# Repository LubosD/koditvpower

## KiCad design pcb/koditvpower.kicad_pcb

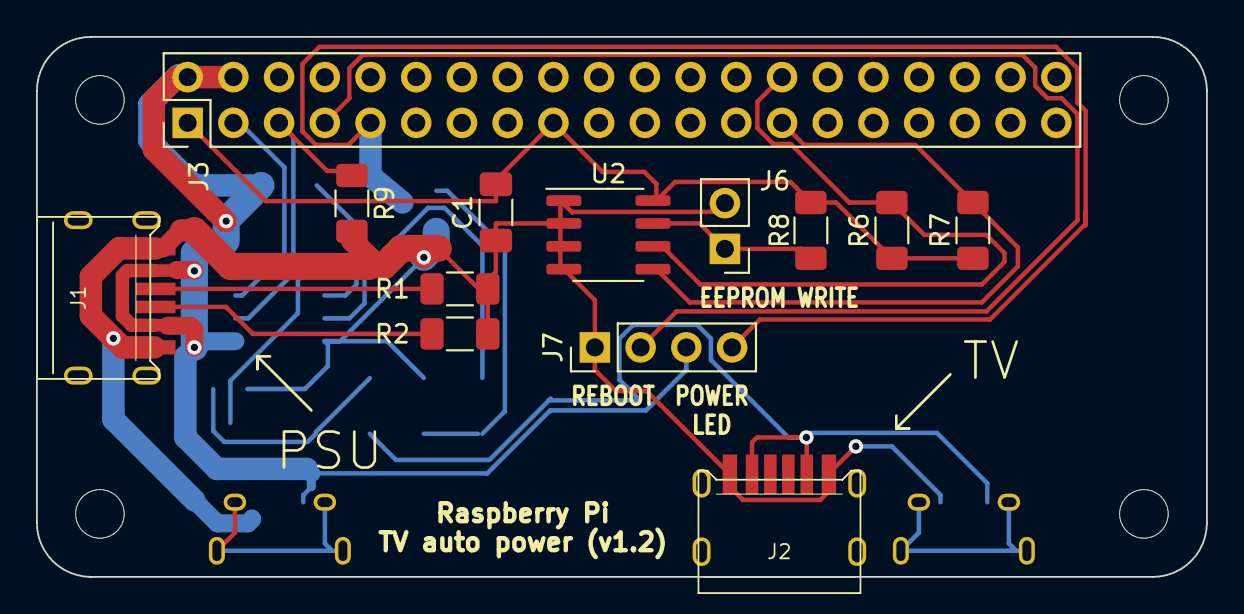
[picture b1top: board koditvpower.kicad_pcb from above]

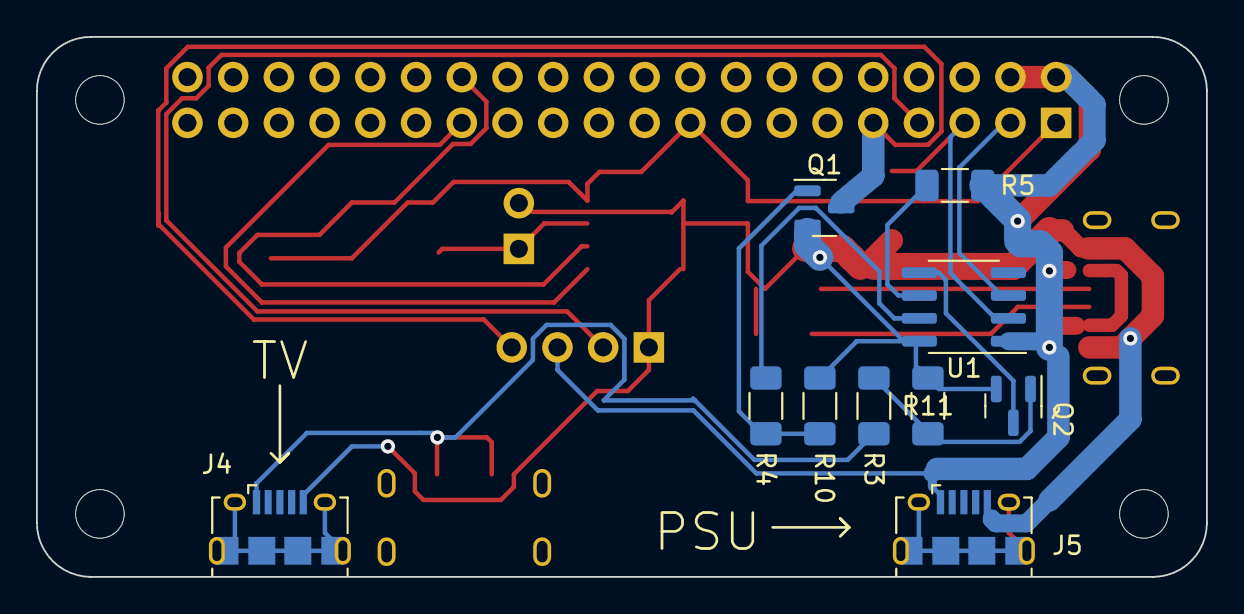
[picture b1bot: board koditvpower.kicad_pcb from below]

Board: 2 copper layers, 65.0 x 30.0 mm, 27 parts (10 on the bottom side), 18 nets.

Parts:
C1: C 100n; C_1206_3216Metric_Pad1.33x1.80mm_HandSolder
H1, H2, H3, H4: MountingHole_2.7mm_M2.5
J1: USB_C_MAIN; TYPE-C-31-M-17_handsolder
J2: USB_C_TV; TYPE-C-31-M-17_handsolder
J3: Raspberry_Pi_2_3; PinHeader_2x20_P2.54mm_Vertical
J4: USB_B_Micro_TV; USB_Micro-B_Amphenol_10118194_Horizontal
J5: USB_B_Micro_MAIN; USB_Micro-B_Amphenol_10118194_Horizontal
J6: EEPROM WRITE; PinHeader_1x02_P2.54mm_Vertical
J7: POWER LED / REBOOT KEY; PinHeader_1x04_P2.54mm_Vertical
Q1: AO3400; SOT-23
Q2: BSS138; SOT-23
R1, R2: R 5k1; R_1206_3216Metric_Pad1.30x1.75mm_HandSolder
R3: R1k; R_1206_3216Metric_Pad1.30x1.75mm_HandSolder
R4: R 1k; R_1206_3216Metric_Pad1.30x1.75mm_HandSolder
R5, R9, R10, R11: R10k; R_1206_3216Metric_Pad1.30x1.75mm_HandSolder
R6, R7: R 3.9K; R_1206_3216Metric_Pad1.30x1.75mm_HandSolder
R8: R 1K; R_1206_3216Metric_Pad1.30x1.75mm_HandSolder
U1: ATtiny412-SS; SOIC-8_3.9x4.9mm_P1.27mm
U2: CAT24C32WI-GT3; SOIC-8_3.9x4.9mm_P1.27mm

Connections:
+3V3: C1.2, J3.1 (3V3), J3.17 (3V3), R6.1, R7.1, R8.1, U2.8 (VCC)
+5V: J1.A9 (VBUS), J1.B9 (VBUS), J3.2 (5V), J3.4 (5V), J5.1 (VBUS), J7.3, R5.2, U1.1 (VCC)
GND: C1.1, J1.A12 (GND), J1.B12 (GND), J2.A12 (GND), J2.B12 (GND), J4.5 (GND), J5.5 (GND), J6.2, J7.1, Q1.2 (S), Q2.2 (S), R1.2, R2.2, R9.2, R10.2, R11.2, U1.8 (GND), U2.1 (A0), U2.2 (A1), U2.3 (A2), U2.4 (GND)
unnamed: J1.A5 (CC1), R1.1
unnamed: J1.B5 (CC2), R2.1
unnamed: J2.A9 (VBUS), J2.B9 (VBUS), J4.1 (VBUS), R3.1
unnamed: J3.9 (GND), J7.4, Q1.3 (D)
unnamed: J6.1, R8.2, U2.7 (WP)
unnamed: Q1.1 (G), R4.2, R10.1
unnamed: Q2.1 (G), R3.2, R11.1
unnamed: Q2.3 (D), U1.5 (PA2)
unnamed: R4.1, U1.7 (PA3)
unnamed: R5.1, U1.6 (~RESET/PA0)
eeprom_sc: J3.28 (ID_SC/GPIO1), R6.2, U2.6 (SCL)
eeprom_sd: J3.27 (ID_SD/GPIO0), R7.2, U2.5 (SDA)
gpio_poweroff: J3.5 (SCL/GPIO3), R9.1, U1.2 (PA6)
gpio_reboot: J3.7 (GCLK0/GPIO4), J7.2
gpio_shutdown: J3.3 (SDA/GPIO2), U1.3 (PA7)

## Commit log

2023-01-26 First working version of EEPROM
2023-01-27 Add Kodi keymap file
2023-01-27 Change poweroff pin
